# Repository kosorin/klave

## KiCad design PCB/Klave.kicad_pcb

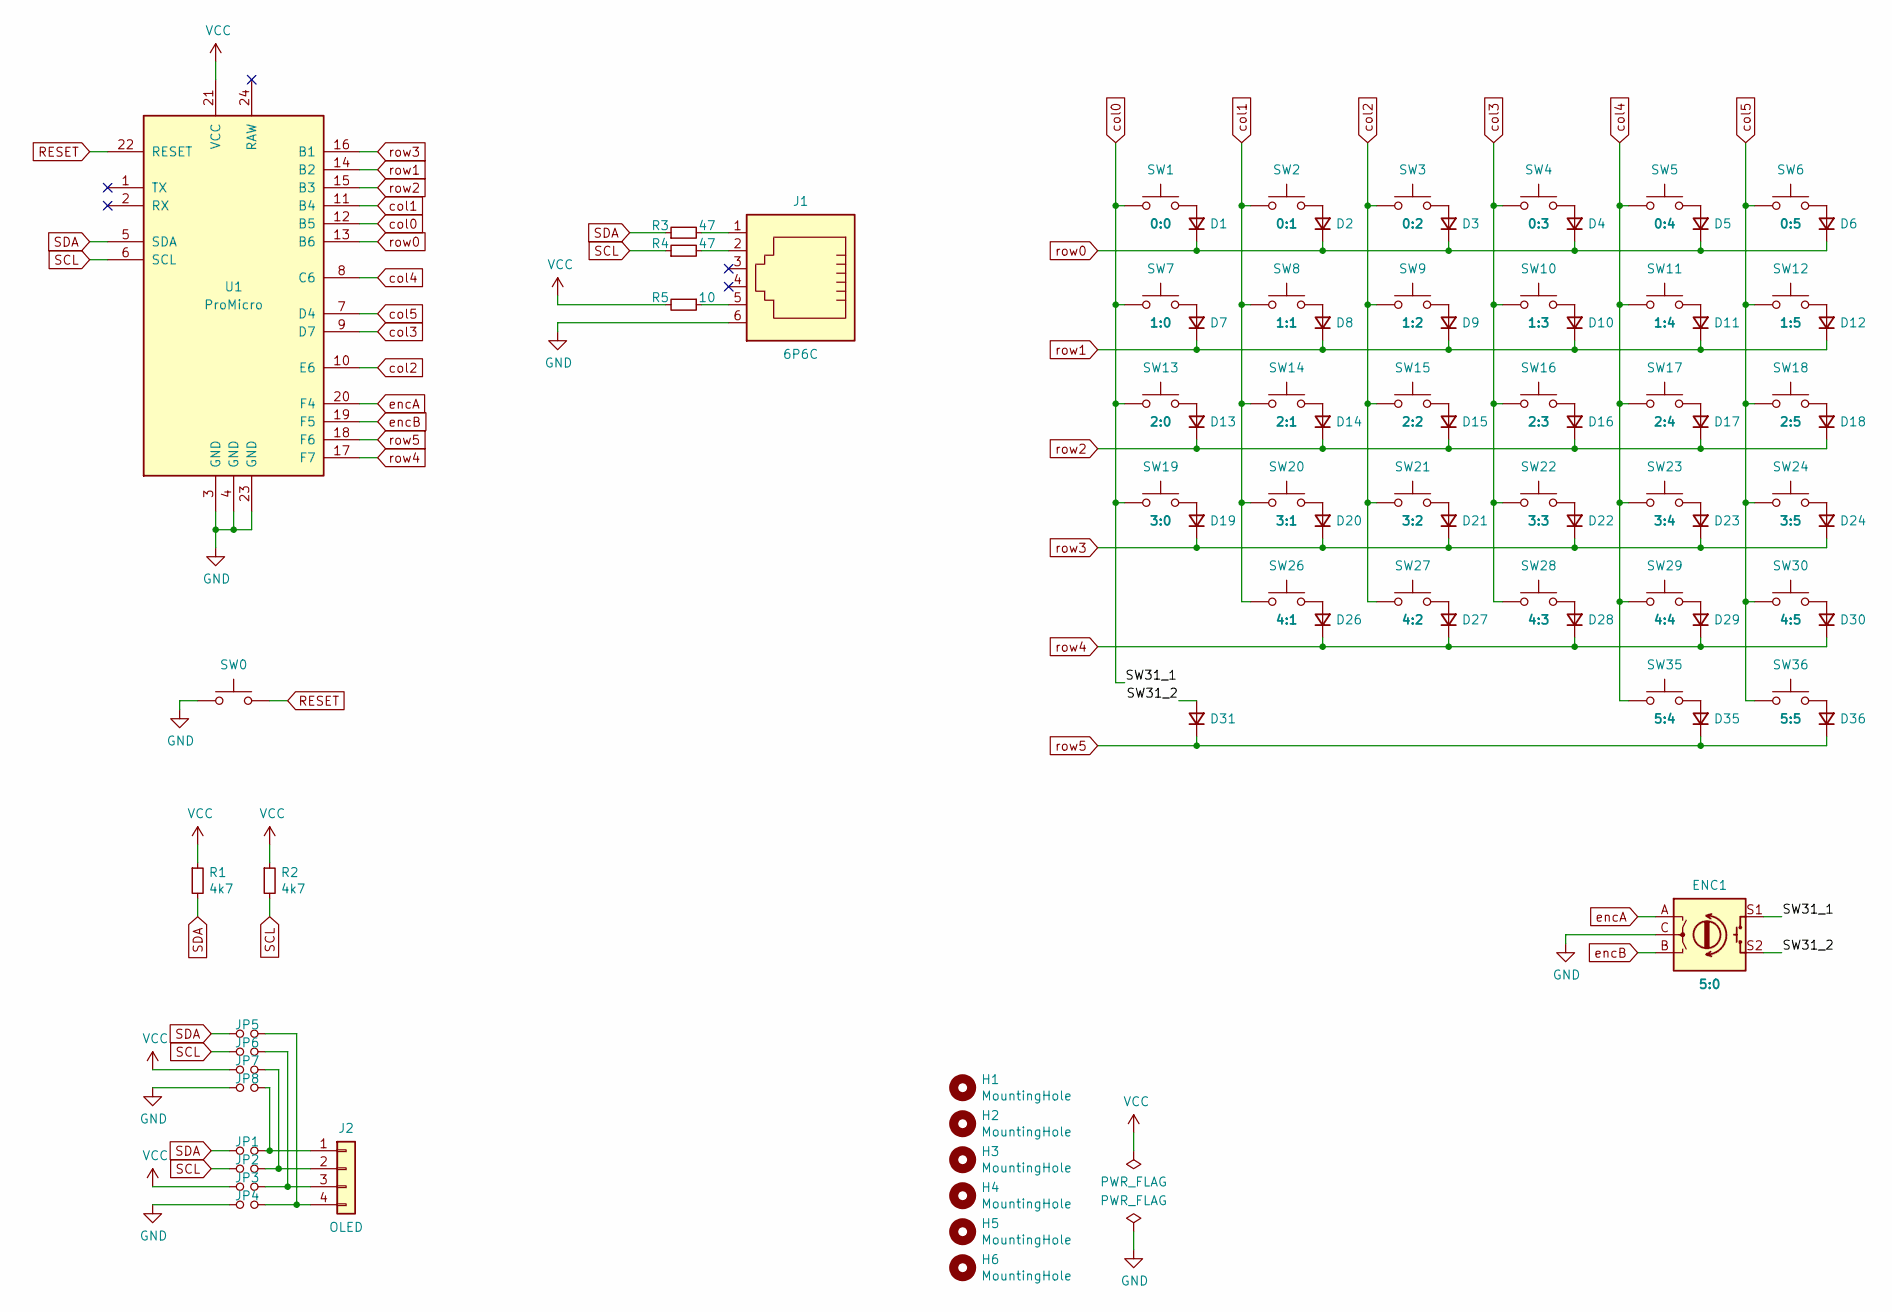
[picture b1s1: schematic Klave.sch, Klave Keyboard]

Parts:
D1: 0:0; D_SOD-123
D2: 0:1; D_SOD-123
D3: 0:2; D_SOD-123
D4: 0:3; D_SOD-123
D5: 0:4; D_SOD-123
D6: 0:5; D_SOD-123
D7: 1:0; D_SOD-123
D8: 1:1; D_SOD-123
D9: 1:2; D_SOD-123
D10: 1:3; D_SOD-123
D11: 1:4; D_SOD-123
D12: 1:5; D_SOD-123
D13: 2:0; D_SOD-123
D14: 2:1; D_SOD-123
D15: 2:2; D_SOD-123
D16: 2:3; D_SOD-123
D17: 2:4; D_SOD-123
D18: 2:5; D_SOD-123
D19: 3:0; D_SOD-123
D20: 3:1; D_SOD-123
D21: 3:2; D_SOD-123
D22: 3:3; D_SOD-123
D23: 3:4; D_SOD-123
D24: 3:5; D_SOD-123
D26: 4:1; D_SOD-123
D27: 4:2; D_SOD-123
D28: 4:3; D_SOD-123
D29: 4:4; D_SOD-123
D30: 4:5; D_SOD-123
D31: 5:0; D_SOD-123
D35: 5:4; D_SOD-123
D36: 5:5; D_SOD-123
ENC1: 5:0; RotaryEncoder_EC11E-Switch
H1, H2, H3, H4, H5, H6: MountingHole; MountingHole_4.8mm_4.5mm
J1: 6P6C; RJ12_6P6C
J2: OLED; Display_OLED_128x32
JP1, JP2, JP3, JP4: Front; SolderJumper-2_P1.3mm_Open_Pad1.0x1.5mm
JP5, JP6, JP7, JP8: Back; SolderJumper-2_P1.3mm_Open_Pad1.0x1.5mm
R1, R2: 4k7; R_1206_3216Metric
R3, R4: 47; R_1206_3216Metric
R5: 10; R_1206_3216Metric
SW0: Reset; SW_Tactile_2pin
SW1: 0:0; SW_Socket_MX
SW2: 0:1; SW_Socket_MX
SW3: 0:2; SW_Socket_MX
SW4: 0:3; SW_Socket_MX
SW5: 0:4; SW_Socket_MX
SW6: 0:5; SW_Socket_MX
SW7: 1:0; SW_Socket_MX
SW8: 1:1; SW_Socket_MX
SW9: 1:2; SW_Socket_MX
SW10: 1:3; SW_Socket_MX
SW11: 1:4; SW_Socket_MX
SW12: 1:5; SW_Socket_MX
SW13: 2:0; SW_Socket_MX
SW14: 2:1; SW_Socket_MX
SW15: 2:2; SW_Socket_MX
SW16: 2:3; SW_Socket_MX
SW17: 2:4; SW_Socket_MX
SW18: 2:5; SW_Socket_MX
SW19: 3:0; SW_Socket_MX
SW20: 3:1; SW_Socket_MX
SW21: 3:2; SW_Socket_MX
SW22: 3:3; SW_Socket_MX
SW23: 3:4; SW_Socket_MX
SW24: 3:5; SW_Socket_MX
SW26: 4:1; SW_Socket_MX
SW27: 4:2; SW_Socket_MX
SW28: 4:3; SW_Socket_MX
SW29: 4:4; SW_Socket_MX
SW30: 4:5; SW_Socket_MX
SW35: 5:4; SW_Socket_MX
SW36: 5:5; SW_Socket_MX
U1: ProMicro; Arduino_ProMicro

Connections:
/SW31_2: D31.2 (A), ENC1.S2
GND: ENC1.C, J1.6, JP4.2, JP8.2, SW0.1, U1.3 (GND), U1.4 (GND), U1.23 (GND)
unnamed: D1.2 (A), SW1.2
unnamed: D2.2 (A), SW2.2
unnamed: D3.2 (A), SW3.2
unnamed: D4.2 (A), SW4.2
unnamed: D5.2 (A), SW5.2
unnamed: D6.2 (A), SW6.2
unnamed: D7.2 (A), SW7.2
unnamed: D8.2 (A), SW8.2
unnamed: D9.2 (A), SW9.2
unnamed: D10.2 (A), SW10.2
unnamed: D11.2 (A), SW11.2
unnamed: D12.2 (A), SW12.2
unnamed: D13.2 (A), SW13.2
unnamed: D14.2 (A), SW14.2
unnamed: D15.2 (A), SW15.2
unnamed: D16.2 (A), SW16.2
unnamed: D17.2 (A), SW17.2
unnamed: D18.2 (A), SW18.2
unnamed: D19.2 (A), SW19.2
unnamed: D20.2 (A), SW20.2
unnamed: D21.2 (A), SW21.2
unnamed: D22.2 (A), SW22.2
unnamed: D23.2 (A), SW23.2
unnamed: D24.2 (A), SW24.2
unnamed: D26.2 (A), SW26.2
unnamed: D27.2 (A), SW27.2
unnamed: D28.2 (A), SW28.2
unnamed: D29.2 (A), SW29.2
unnamed: D30.2 (A), SW30.2
unnamed: D35.2 (A), SW35.2
unnamed: D36.2 (A), SW36.2
unnamed: J1.1, R3.2
unnamed: J1.2, R4.2
unnamed: J1.5, R5.1
unnamed: J2.1, JP1.1, JP8.1
unnamed: J2.2, JP2.1, JP7.1
unnamed: J2.3, JP3.1, JP6.1
unnamed: J2.4, JP4.1, JP5.1
RESET: SW0.2, U1.22 (RESET)
SCL: JP2.2, JP6.2, R2.2, R4.1, U1.6 (SCL)
SDA: JP1.2, JP5.2, R1.2, R3.1, U1.5 (SDA)
VCC: JP3.2, JP7.2, R1.1, R2.1, R5.2, U1.21 (VCC)
col0: ENC1.S1, SW1.1, SW7.1, SW13.1, SW19.1, U1.12 (B5)
col1: SW2.1, SW8.1, SW14.1, SW20.1, SW26.1, U1.11 (B4)
col2: SW3.1, SW9.1, SW15.1, SW21.1, SW27.1, U1.10 (E6)
col3: SW4.1, SW10.1, SW16.1, SW22.1, SW28.1, U1.9 (D7)
col4: SW5.1, SW11.1, SW17.1, SW23.1, SW29.1, SW35.1, U1.8 (C6)
col5: SW6.1, SW12.1, SW18.1, SW24.1, SW30.1, SW36.1, U1.7 (D4)
encA: ENC1.A, U1.20 (F4)
encB: ENC1.B, U1.19 (F5)
row0: D1.1 (K), D2.1 (K), D3.1 (K), D4.1 (K), D5.1 (K), D6.1 (K), U1.13 (B6)
row1: D7.1 (K), D8.1 (K), D9.1 (K), D10.1 (K), D11.1 (K), D12.1 (K), U1.14 (B2)
row2: D13.1 (K), D14.1 (K), D15.1 (K), D16.1 (K), D17.1 (K), D18.1 (K), U1.15 (B3)
row3: D19.1 (K), D20.1 (K), D21.1 (K), D22.1 (K), D23.1 (K), D24.1 (K), U1.16 (B1)
row4: D26.1 (K), D27.1 (K), D28.1 (K), D29.1 (K), D30.1 (K), U1.17 (F7)
row5: D31.1 (K), D35.1 (K), D36.1 (K), U1.18 (F6)

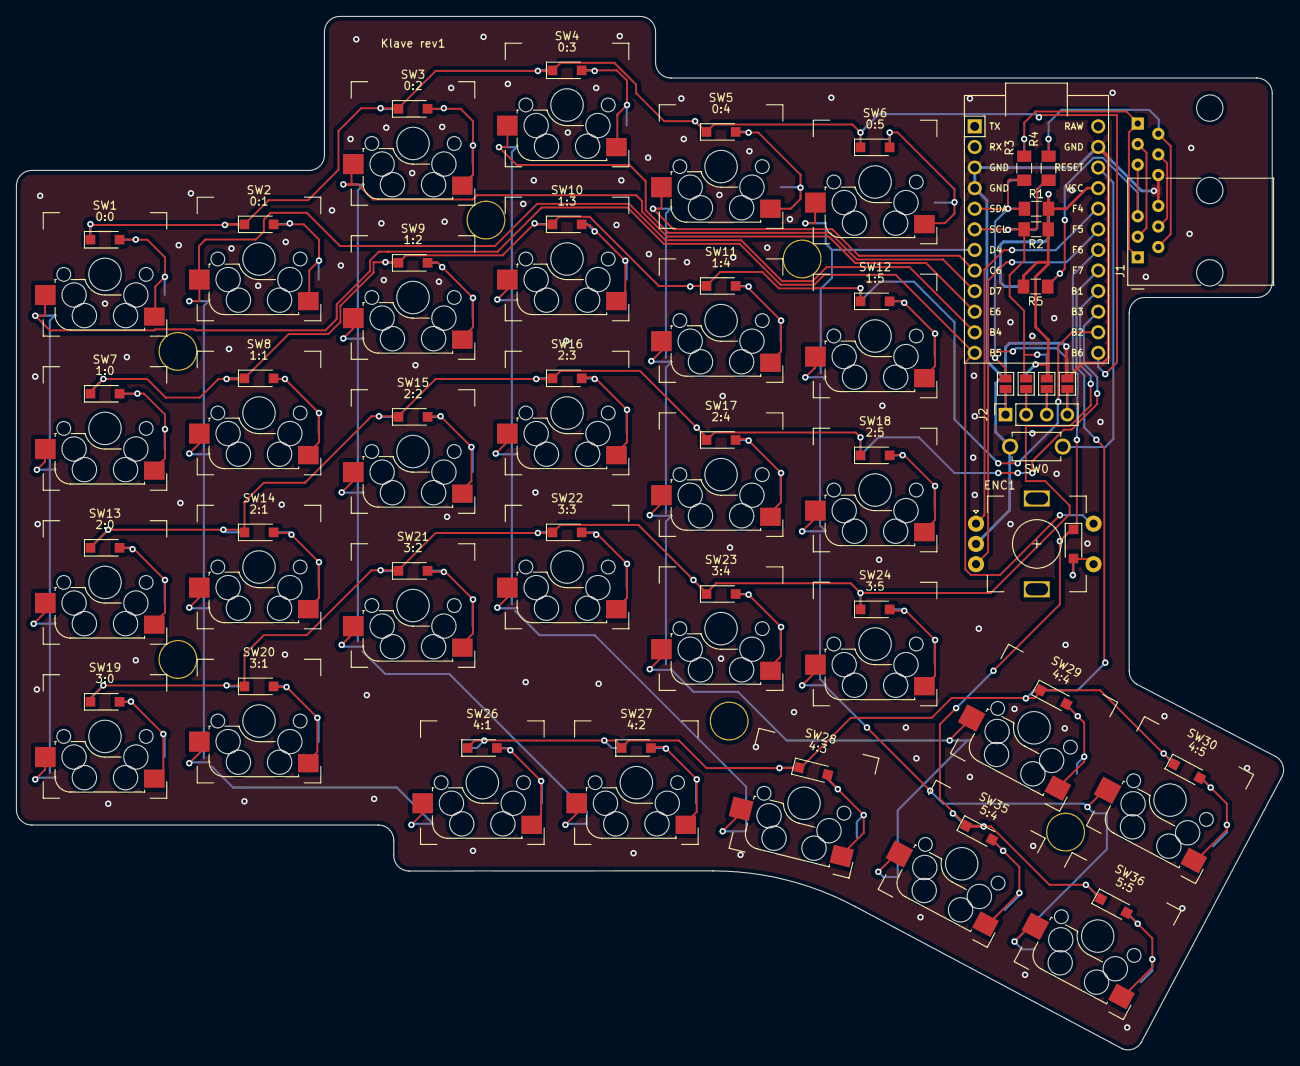
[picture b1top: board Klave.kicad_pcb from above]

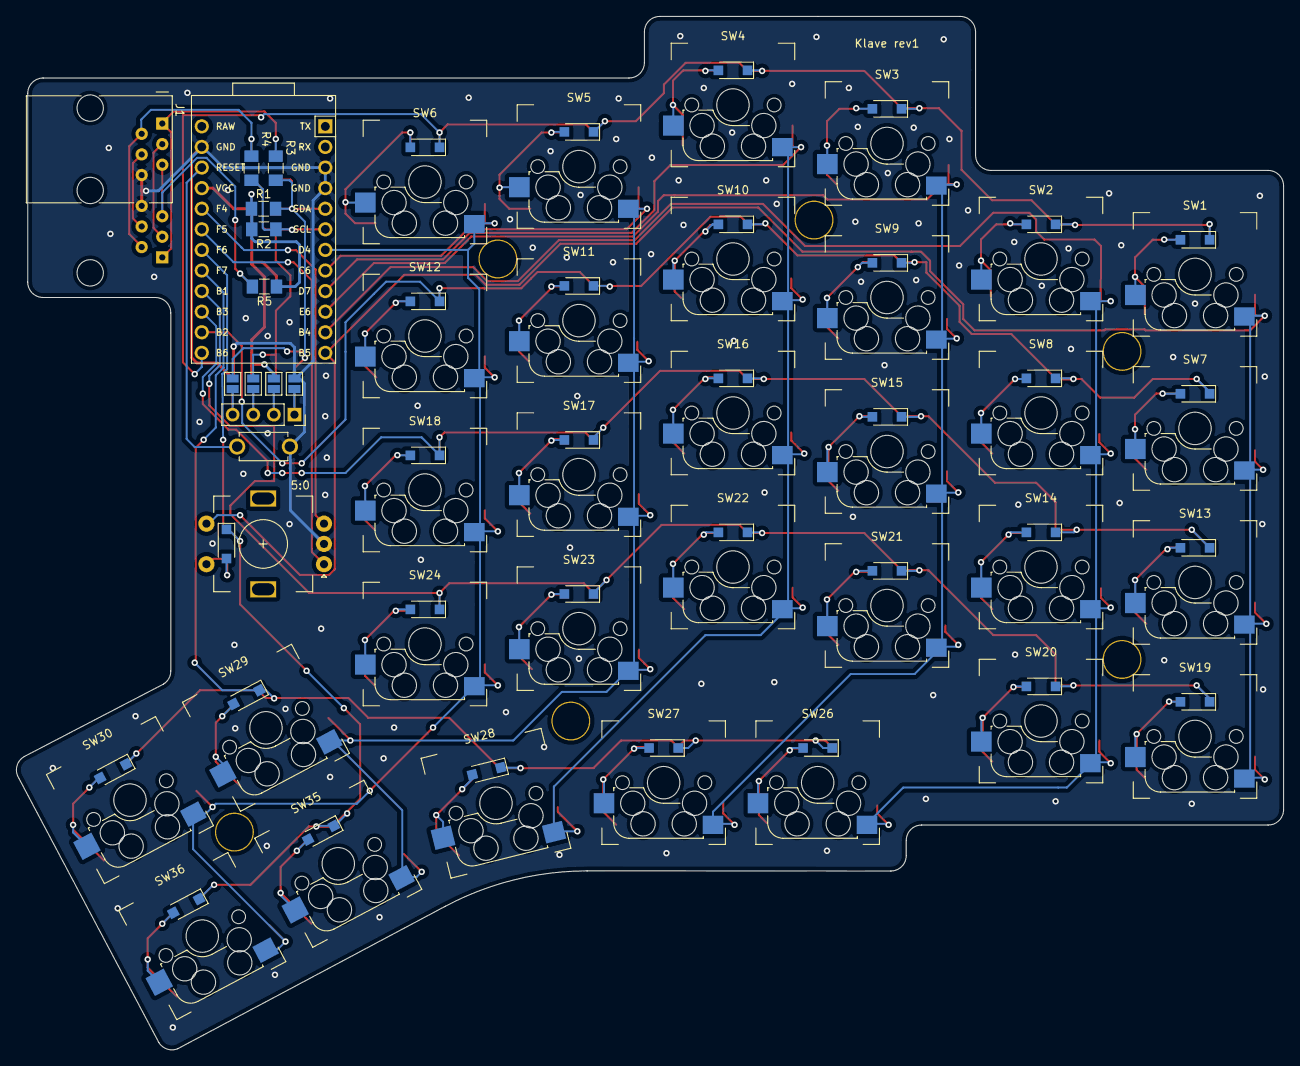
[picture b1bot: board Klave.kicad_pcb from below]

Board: 2 copper layers, 156.3 x 127.5 mm, 87 parts (4 on the bottom side), 58 nets.

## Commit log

2020-08-09 Add PCB .gitignore
2020-08-09 Add empty PCB project
2020-08-09 Copy ProMicro symbol from keebio-components
2020-08-23 Update ProMicro symbol pin labels
2020-08-23 Add TRRS symbol
2020-08-23 Create schematic without keys
2020-08-25 Add key matrix
2020-08-25 Add rotary encoder switch
2020-08-27 Edit schematic
2020-08-27 Add footprint library
2020-08-27 Add TRRS footprints
2020-08-28 Annotate schematic symbols
2020-08-28 Fix schematic symbol reference
2020-08-28 Rename key diodes
2020-08-28 Remove 3D model path
2020-08-29 Add ProMicro footprint
2020-08-29 Add rotary encoder footprint
2020-08-29 Edit schematic page settings
2020-08-29 Add resistor footprint
2020-08-29 Unify footprint styles
2020-08-29 Rotate resistor 3D model
2020-08-29 Add ProMicro 3D model
2020-08-29 Add rotary encoder 3D model
2020-08-29 Add keyboard switch footprint including 3D models
2020-08-30 Remove TRRS connector
    Will be replaced with RJ11 or similar connector.
2020-08-30 Add diode footrpint
2020-08-30 Add 2 pin tactile switch footprint
2020-08-30 Change 3D models folder structure
2020-08-30 Rotate diode 3D model
2020-08-30 Add paste to diode through-hole pads
2020-08-30 Add OLED display footprint
2020-08-30 Remove TRRS schematic symbol
2020-08-30 Drop serial communication support
2020-08-30 Split OLED display footprint into 128x32 and 128x64 variants
2020-08-30 Remove connector from schematic
2020-08-31 Remove I2C pull-up resistor jumpers
2020-08-31 Remake ProMicro schematic symbol
    Reorder pins to functional pin order.
2020-08-31 Update ProMicro footprint pin names
2020-08-31 Set schematic symbols values
2020-08-31 Assign PCB footprints to schematic symbols
2020-09-01 Fix rotary encoder footprint courtyard
2020-09-01 Change display symbol value from "Display" to "OLED"
2020-09-01 Set default ProMicro symbol datasheet value
2020-09-01 Add RJ12 schematic symbol and footprint
2020-09-02 Change rotary encoder reference name from SW to ENC
2020-09-02 Rename switch files
2020-09-02 Add keycap 3D model
2020-09-02 Set diode footprint fabrication attribute to "through hole"
2020-09-03 Set keycap borders
2020-09-03 Add rotary encoder knob 3D model
2020-09-03 Create key layout
2020-09-04 Change ProMicro schematic symbol text fields position and size
2020-09-04 Apply schematic "best practices"
2020-09-04 Add connector protective resistors
2020-09-04 Fix display jumpers
2020-09-04 Replace through-hole mounting resistor with surface mounting resistor
2020-09-04 Use SMD pads for diode instead of through-hole pads with paste
2020-09-04 Update ProMicro footprint courtyard
2020-09-04 Swap switch socket back pads number
2020-09-04 Hide diode reference field on silk layers
2020-09-04 Fix SMD footprints
2020-09-05 Create first PCB prototype
2020-09-06 Fix footprint courtlayrds
2020-09-06 Update PCB footprints from library
2020-09-06 Add edge cuts
2020-09-06 Improve PCB edge cuts
2020-09-07 Update rotary encoder footprint to match switch footprint
2020-09-07 Improve PCB edge cuts and update footprints from library
2020-09-10 Add mounting holes
2020-09-10 Add net class for power (VCC and GND)
2020-09-16 Add GND vias
2020-09-19 Lower switch pad size
2020-09-19 Fix DRC errors
2020-09-20 Add gbrjob to gitignore
2020-09-20 Generate gerber files
2020-09-20 Update schematic and PCB page settings
2020-09-20 Add Gerber to gitignore
2020-09-20 Remove auxiliary axis origin
2020-09-20 Remove circles from edge cuts layer
2020-09-20 Add more vias
2020-09-20 Add plate mounting hole footprint
2020-09-20 Add bottom plate
2020-09-20 Add plate switch footprint
2020-09-20 Add plate rotary encoder footprint
2020-09-20 Prepare top plate
2020-09-20 Add switch and rotary encoder edge cuts to top plate
2020-09-20 Remove top plate above ProMicro
2020-09-20 Update top plate PCB page settings
2024-07-20 Create LICENSE
2024-07-24 Create empty project
2024-07-24 Add empty .gitmodules
2024-07-24 Add ki-lime-pi-pico submodule
2024-07-24 Update lib tables
2024-07-25 Update ki-lime-pi-pico submodule
2024-07-25 Set schematic page settings
2024-07-26 Update schmatic
    - matrix
    - pico
    - reset button
    - TRRS connector
2024-07-26 Rename libs directory to lib
2024-07-27 Pull up a pin for handedness
2024-07-27 Swap TX and RX on TRRS
2024-07-27 Add right half
2024-07-27 Shift rows by one pin
